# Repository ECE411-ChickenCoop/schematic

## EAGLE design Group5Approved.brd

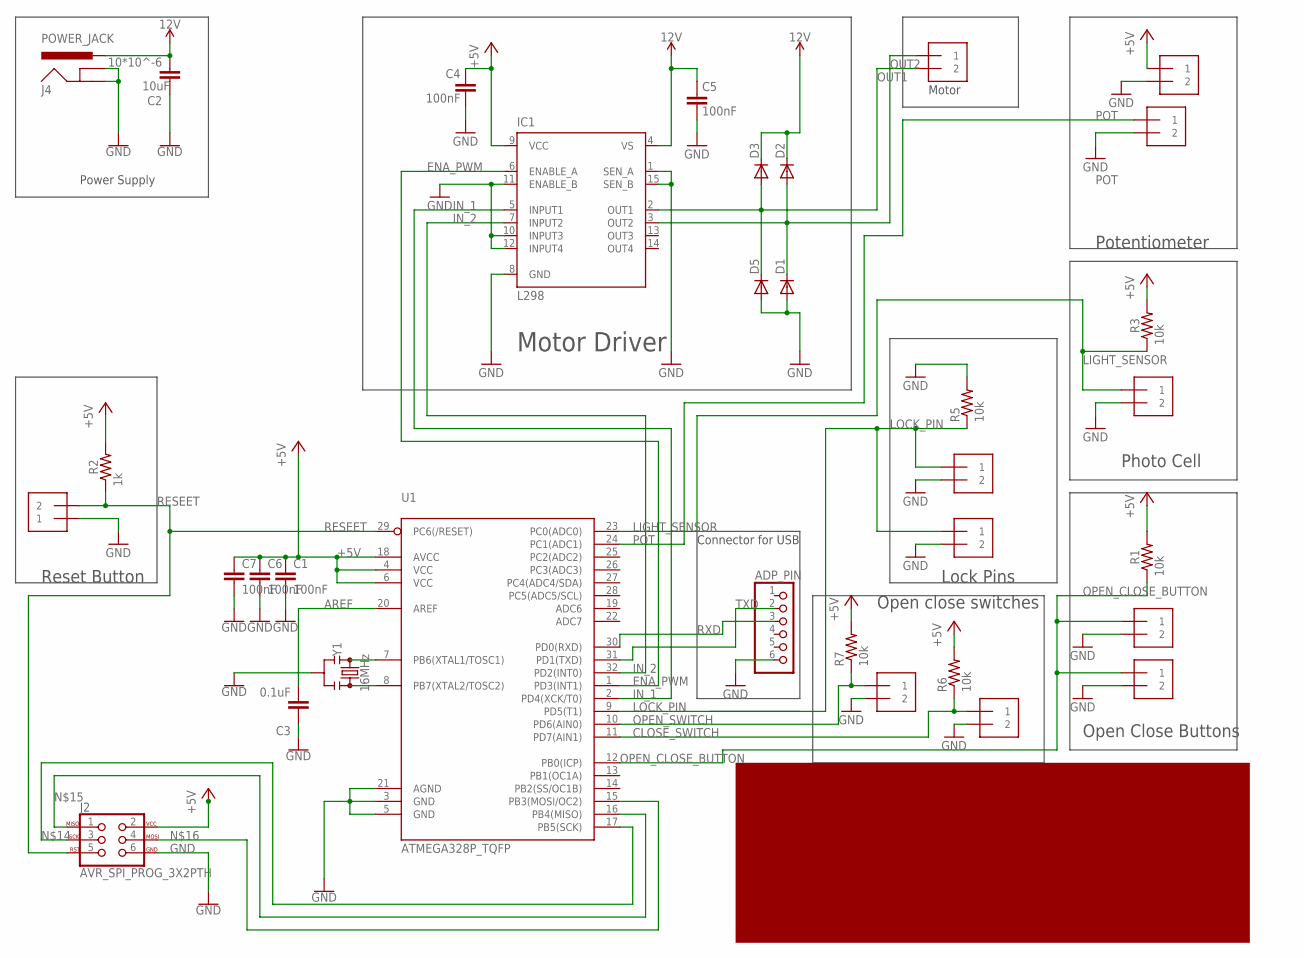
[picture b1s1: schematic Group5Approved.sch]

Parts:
ADP_PIN: PINHD-1X6; 1X06
C1, C4, C5, C6, C7: 100nF; C0805
C2: 10*10^-6; C0805
C3: 0.1uF; C0805
CLOSESWITCH: 1X2-3.5MM
D1, D2, D3, D5: DIODE-DO214AA; DO214AA
IC1: L298; MULTIWATT-15
INSIDE_BUTTON: 1X2-3.5MM
J2: AVR_SPI_PROG_3X2PTH; 2X3
J4: POWER_JACK; POWER_JACK_PTH
LIGHT_SENSOR: 1X2-3.5MM
LOCK_PIN1, LOCK_PIN2: 1X2-3.5MM
MOTOR: 1X2-3.5MM
OPEN_SWITCH: 1X2-3.5MM
OUTSIDE_BUTTON: 1X2-3.5MM
POT: 1X2-3.5MM
POTPOWER: 1X2-3.5MM
R1, R3, R5, R6, R7: 10k; M0805
R2: 1k; M0805
RESETBUTTON: 1X2-3.5MM
U1: ATMEGA328P_TQFP; TQFP32-08
Y1: 16MHz; RESONATOR-SMD-3.2X1.3

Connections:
12V: C2.2, C5.1, D2.C, D3.C, IC1.4 (VS), J4.PWR
+5V: C1.1, C4.1, C6.1, C7.1, IC1.9 (VCC), J2.2, POTPOWER.1, R1.2, R2.2, R3.2, R6.2, R7.2, U1.4 (VCC), U1.6 (VCC), U1.18 (AVCC)
AREF: C3.2, U1.20 (AREF)
CLOSE_SWITCH: CLOSESWITCH.1, R6.1, U1.11 (PD7(AIN1))
ENA_PWM: IC1.6 (ENABLE_A), U1.1 (PD3(INT1))
GND: ADP_PIN.6, C1.2, C2.1, C3.1, C4.2, C5.2, C6.2, C7.2, CLOSESWITCH.2, D1.A, D5.A, IC1.1 (SEN_A), IC1.8 (GND), IC1.10 (INPUT3), IC1.11 (ENABLE_B), IC1.12 (INPUT4), IC1.15 (SEN_B), INSIDE_BUTTON.2, J2.6, J4.GND, J4.GNDBREAK, LIGHT_SENSOR.2, LOCK_PIN1.2, LOCK_PIN2.2, OPEN_SWITCH.2, OUTSIDE_BUTTON.2, POT.2, POTPOWER.2, R5.2, RESETBUTTON.1, U1.3 (GND), U1.5 (GND), U1.21 (AGND), Y1.2
IN_1: IC1.5 (INPUT1), U1.2 (PD4(XCK/T0))
IN_2: IC1.7 (INPUT2), U1.32 (PD2(INT0))
LIGHT_SENSOR: LIGHT_SENSOR.1, R3.1, U1.23 (PC0(ADC0))
LOCK_PIN: LOCK_PIN1.1, LOCK_PIN2.1, R5.1, U1.9 (PD5(T1))
unnamed: J2.3, U1.17 (PB5(SCK))
unnamed: J2.1, U1.16 (PB4(MISO))
unnamed: J2.4, U1.15 (PB3(MOSI/OC2))
unnamed: U1.7 (PB6(XTAL1/TOSC1)), Y1.1
unnamed: U1.8 (PB7(XTAL2/TOSC2)), Y1.3
OPEN_CLOSE_BUTTON: INSIDE_BUTTON.1, OUTSIDE_BUTTON.1, R1.1, U1.12 (PB0(ICP))
OPEN_SWITCH: OPEN_SWITCH.1, R7.1, U1.10 (PD6(AIN0))
OUT1: D3.A, D5.C, IC1.2 (OUT1), MOTOR.2
OUT2: D1.C, D2.A, IC1.3 (OUT2), MOTOR.1
POT: POT.1, U1.24 (PC1(ADC1))
RESEET: J2.5, R2.1, RESETBUTTON.2, U1.29 (PC6(/RESET))
RXD: ADP_PIN.3, U1.30 (PD0(RXD))
TXD: ADP_PIN.2, U1.31 (PD1(TXD))

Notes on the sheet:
Open Close Buttons
Photo Cell
Potentiometer
Motor
Power Supply
Motor Driver
Lock Pins
Open close switches
Reset Button
Connector for USB

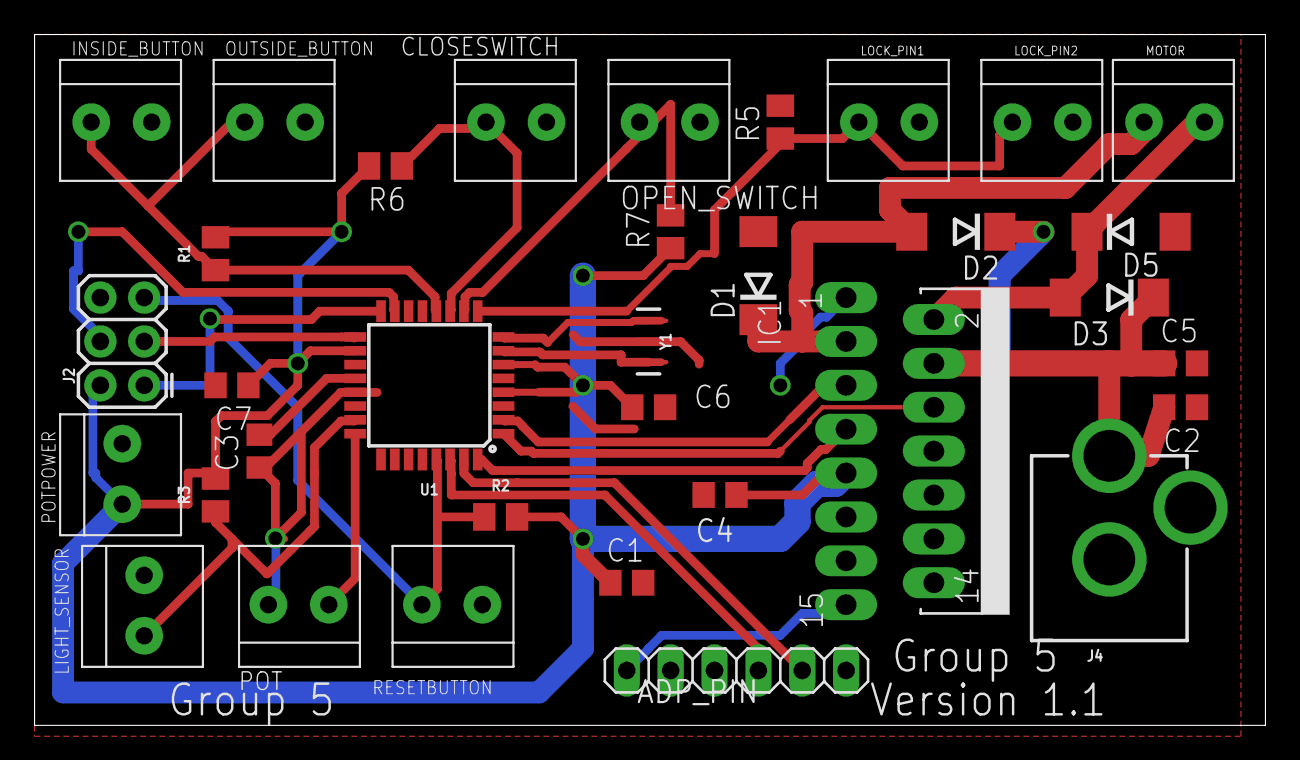
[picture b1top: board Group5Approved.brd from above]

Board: 2 copper layers, 71.3 x 40.0 mm, 34 parts (0 on the bottom side), 23 nets.

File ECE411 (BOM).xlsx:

Bill Of Materials for Team 5 Auto-Chicken Coop Door
source file: V1
Last modified: November 8, 2018
PCB version: V1 |  | P/DNP = | Place/Do Not Place component
BOM revision: 1
Cnt | Part References | P/DNP | Mfg | Mfg PN | Description | Distributor | Dist. PN | Cost Ea. | Cost Ext. | Notes
1 | POWER_JACK | P | CVI Inc. | PJ-202A | CONN PWR JACK 2X5.5MM KINKED PIN | Digikey | CP-202A-ND | 1.25 | 1.25
1 | U1 | P | Microchip | ATMEGA238-AU | IC MCU 32BIT 32KB FLASH 32TQFP | Digikey | ATMEGA328-AU-ND | 1.88 | 1.88
3 | C1, C4, C5 | P | Yageo | CC0805ZRY5V9BB104 | 0.1µF -20%, +80% 50V Ceramic Capacitor Y5V (F) 0805 (2012 Metric) | Digikey | 311-1361-1-ND | 0.16 | 0.48
1 | C2 | P | Samsung | CL21A106KOCLRNC | CAP CER 10UF 16V X5R 0805 | Digikey | 1276-2399-1-ND | 0.25 | 0.25
4 | D1, D2, D3, D5 | P | Littelfuse Inc. | SMBJ15A | TVS DIODE 15V 24.4V DO214AA | Digikey | SMBJ15ALFCT-ND | 0.56000000000000005 | 2.2400000000000002
1 | IC1 | P | STMicroelectronics | L298N | IC BRIDGE DRIVER PAR 15MULTIWATT | Digikey | 497-1395-5-ND | 4.8600000000000003 | 4.8600000000000003
1 | INSIDE_BUTTON | P | On Shore Technology Inc. | ED555/2DS | TERMINAL BLOCK 3.5MM 2POS PCB | Digikey | ED1514-ND | 1.06 | 1.06
1 | INSIDE_OPEN_BUTTON | P | On Shore Technology Inc. | ED555/2DS | TERMINAL BLOCK 3.5MM 2POS PCB | Digikey | ED1514-ND | 1.06 | 1.06
1 | LIGHT_SENSOR | P | On Shore Technology Inc. | ED555/2DS | TERMINAL BLOCK 3.5MM 2POS PCB | Digikey | ED1514-ND | 1.06 | 1.06
1 | LOCK_PIN1 | P | On Shore Technology Inc. | ED555/2DS | TERMINAL BLOCK 3.5MM 2POS PCB | Digikey | ED1514-ND | 1.06 | 1.06
1 | LOCK_PIN2 | P | On Shore Technology Inc. | ED555/2DS | TERMINAL BLOCK 3.5MM 2POS PCB | Digikey | ED1514-ND | 1.06 | 1.06
1 | MOTOR | P | On Shore Technology Inc. | ED555/2DS | TERMINAL BLOCK 3.5MM 2POS PCB | Digikey | ED1514-ND | 1.06 | 1.06
1 | OUTSIDE_BUTTON | P | On Shore Technology Inc. | ED555/2DS | TERMINAL BLOCK 3.5MM 2POS PCB | Digikey | ED1514-ND | 1.06 | 1.06
1 | OUTSIDE_OPEN_BUTTON | P | On Shore Technology Inc. | ED555/2DS | TERMINAL BLOCK 3.5MM 2POS PCB | Digikey | ED1514-ND | 1.06 | 1.06
1 | POT | P | On Shore Technology Inc. | ED555/2DS | TERMINAL BLOCK 3.5MM 2POS PCB | Digikey | ED1514-ND | 1.06 | 1.06
1 | POTPOWER | P | On Shore Technology Inc. | ED555/2DS | TERMINAL BLOCK 3.5MM 2POS PCB | Digikey | ED1514-ND | 1.06 | 1.06
1 | RESETBUTTON | P | On Shore Technology Inc. | ED555/2DS | TERMINAL BLOCK 3.5MM 2POS PCB | Digikey | ED1514-ND | 1.06 | 1.06
1 | J1 | P | Sullins Connector Solutions | PPTC061LFBN-RC | CONN HEADER FEMALE 6POS .1" TIN | Digikey | S7004-ND | 0.52 | 0.52
1 | J2 | P | Harwin Inc. | M20-9720345 | 2X3POS DIL VERTICAL PIN HEADER | Digikey | 952-1921-ND | 0.33 | 0.33
5 | R1, R3, R5, R6, R7 | P | Susumu | RR1220P-103-D | RES SMD 10K OHM 0.5% 1/10W 0805 | Digikey | RR12P10.0KDCT-ND | 0.11 | 0.55000000000000004
1 | R2 | P | Susumu | RR1220P-102-D | RES SMD 1K OHM 0.5% 1/10W 0805 | Digikey | RR12P1.0KDCT-ND | 0.11 | 0.11
1 | Y1 | P | Murata Electronics North America | CSTCE16M0V53-R0 | CER RES 16.0000MHZ 15PF SMD | Digikey | 490-1198-1-ND | 0.5 | 0.5
2 |  | DNP | Aleph | N/A | Door Mounted Reed Switch | Amazon | B00LYCUSBY | 1.44 | 2.88
1 |  | DNP | Pwron | N/A | 9v 2A Power Adapter | Amazon | B07G9NWDKV | 8.99 | 8.99
1 |  | DNP | Greartisan |  | 5 RPM High Torque DC Motor | Amazon | B072N867G3 | 14.99 | 14.99
2 |  | DNP | Atoplee | 15060012S02 | Solenoid Lock | Amazon | B01FH1JCPU | 3.875 | 7.75
2 |  | DNP | Uxcell | a17021400ux0988 | Water Resistant Button | Amazon | B06XR89KN5 | 3.3 | 6.6
1 |  | DNP | Advanced Photonix | PDV-P5003 | PHOTOCELL 12K-58K OHM 11MM | Digikey | PDV-P5003-ND | 2.2200000000000002 | 2.2200000000000002
 |  |  |  |  |  |  | TOTAL COST: |  | 68.059999999999988
Ver # | Changed in version
1 | Initial BOM.

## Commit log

2018-11-08 take 2
    needs traces added
2018-11-09 circuit traced and ready for final approval

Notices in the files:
parts and their libraries:
SparkFun-Connectors: Licensing: Creative Commons ShareAlike 4.0 International - https://creativecommons.org/licenses/by-sa/4.0
